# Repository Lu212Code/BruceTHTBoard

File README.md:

# BruceTHTBoard
Bruce PCB made for simple THT parts and Boards

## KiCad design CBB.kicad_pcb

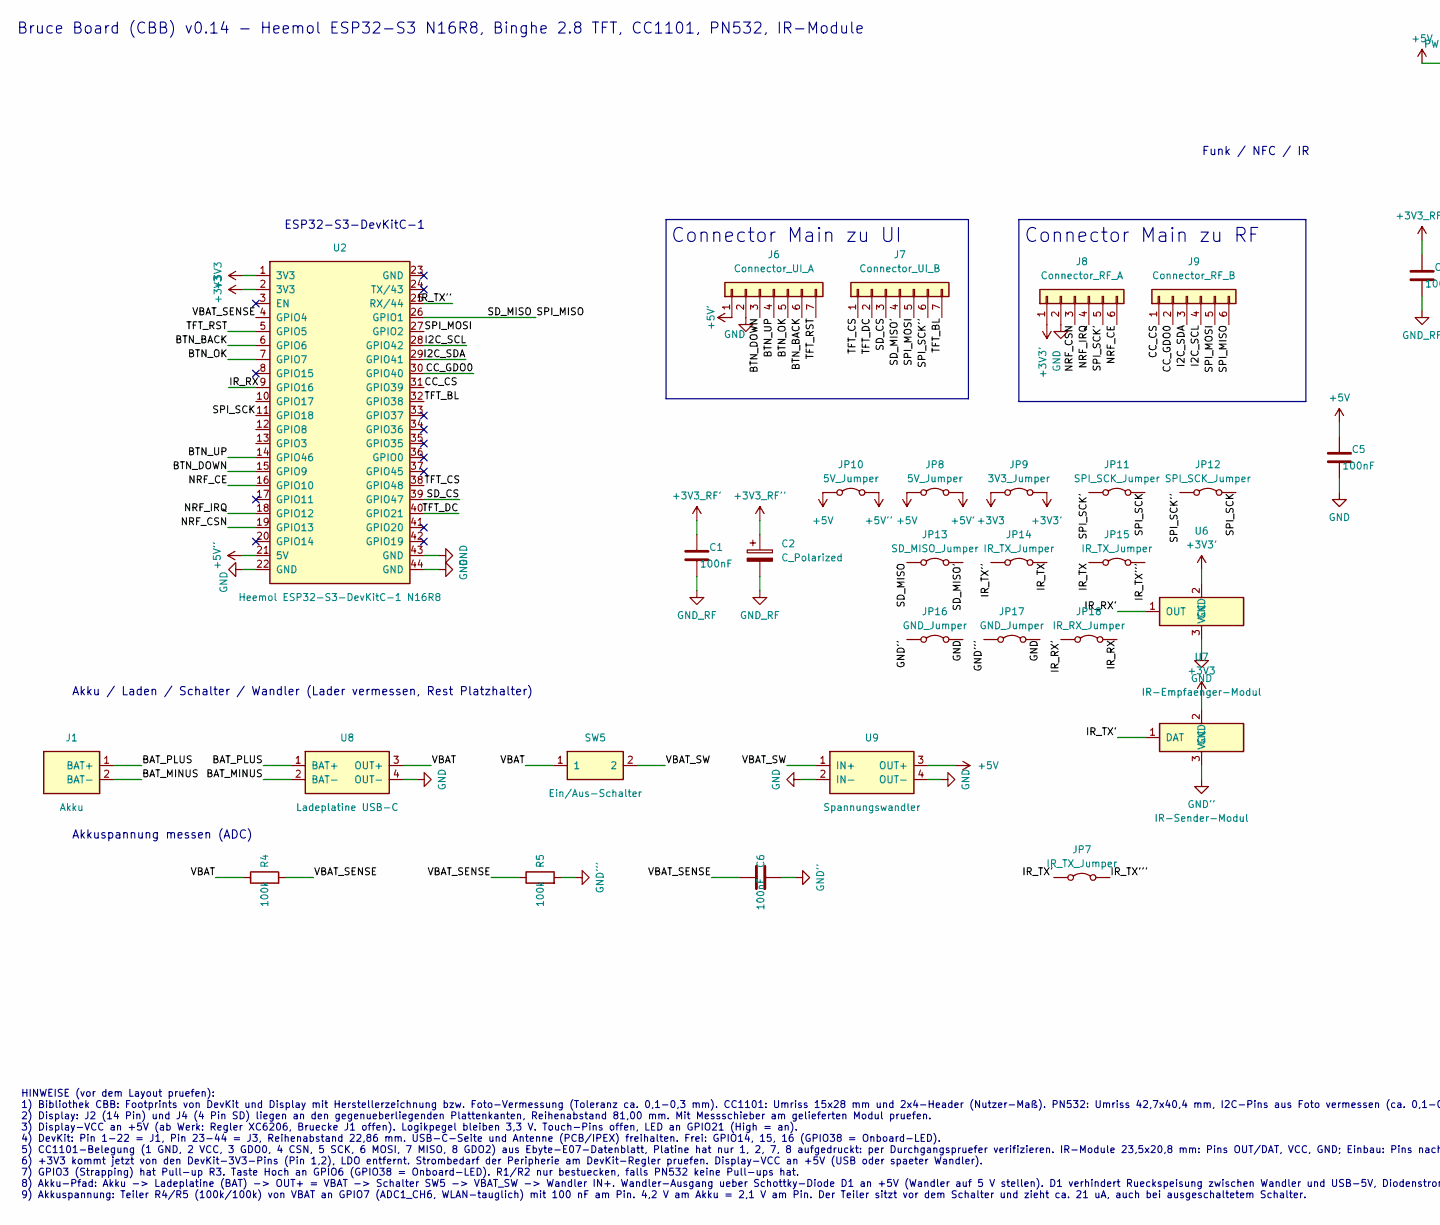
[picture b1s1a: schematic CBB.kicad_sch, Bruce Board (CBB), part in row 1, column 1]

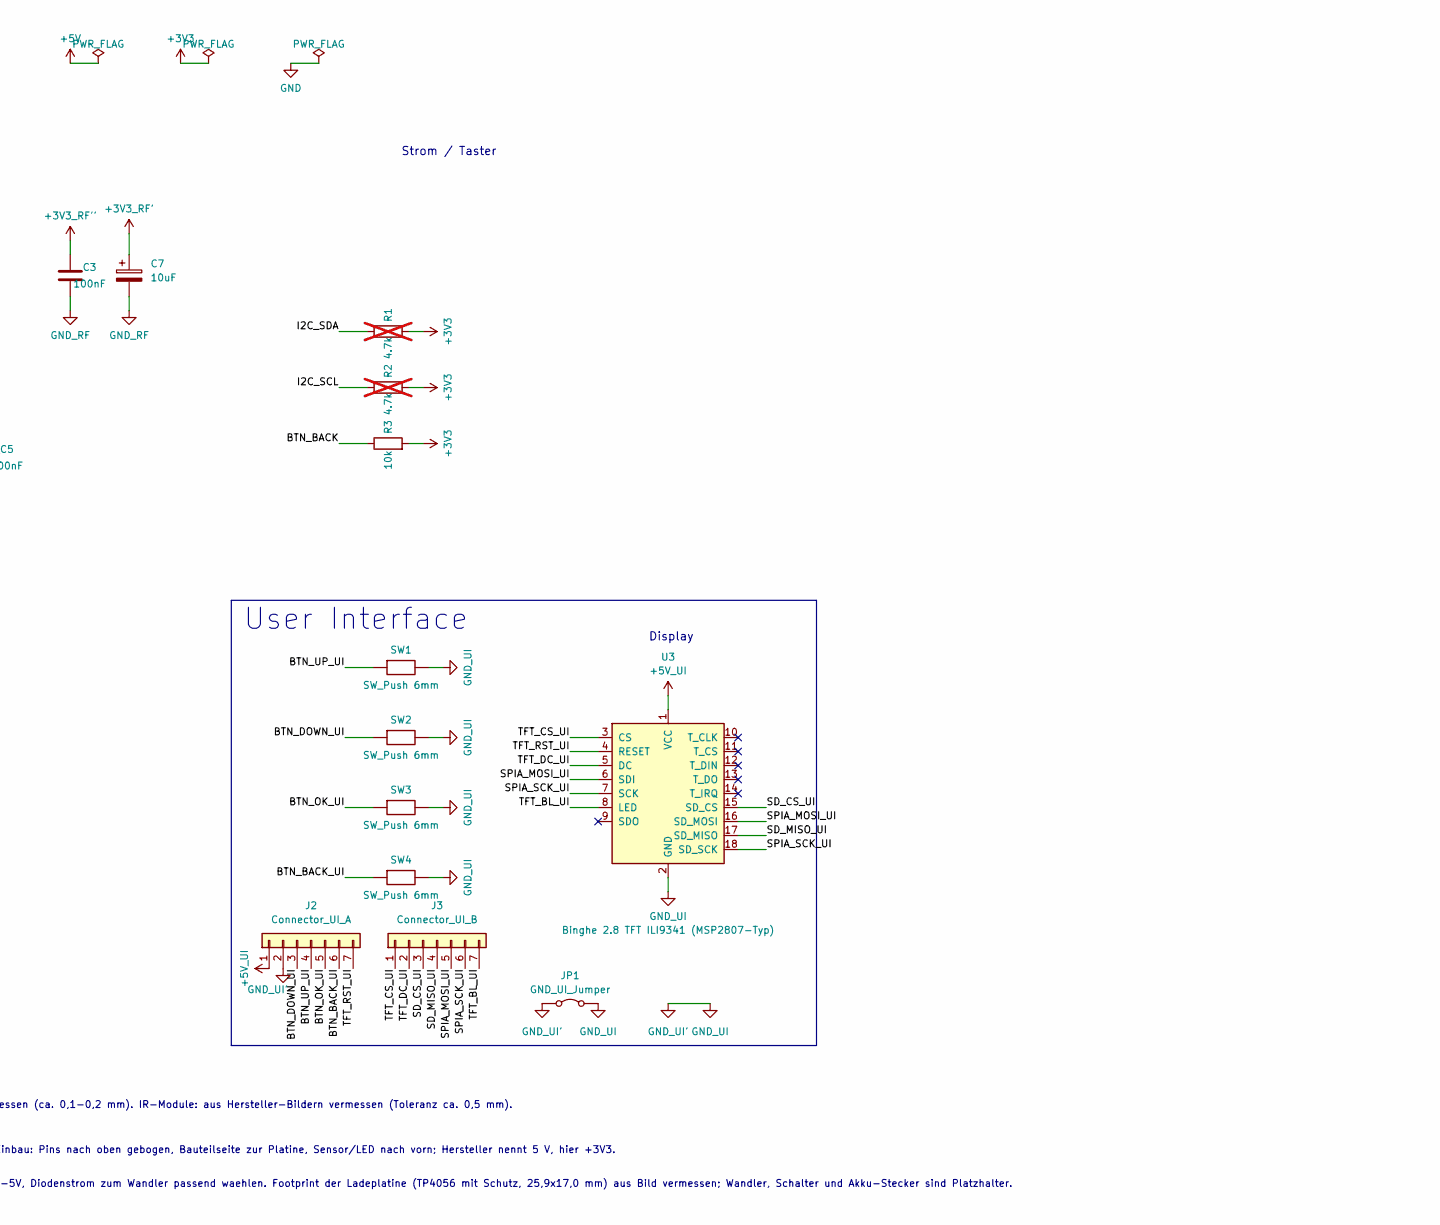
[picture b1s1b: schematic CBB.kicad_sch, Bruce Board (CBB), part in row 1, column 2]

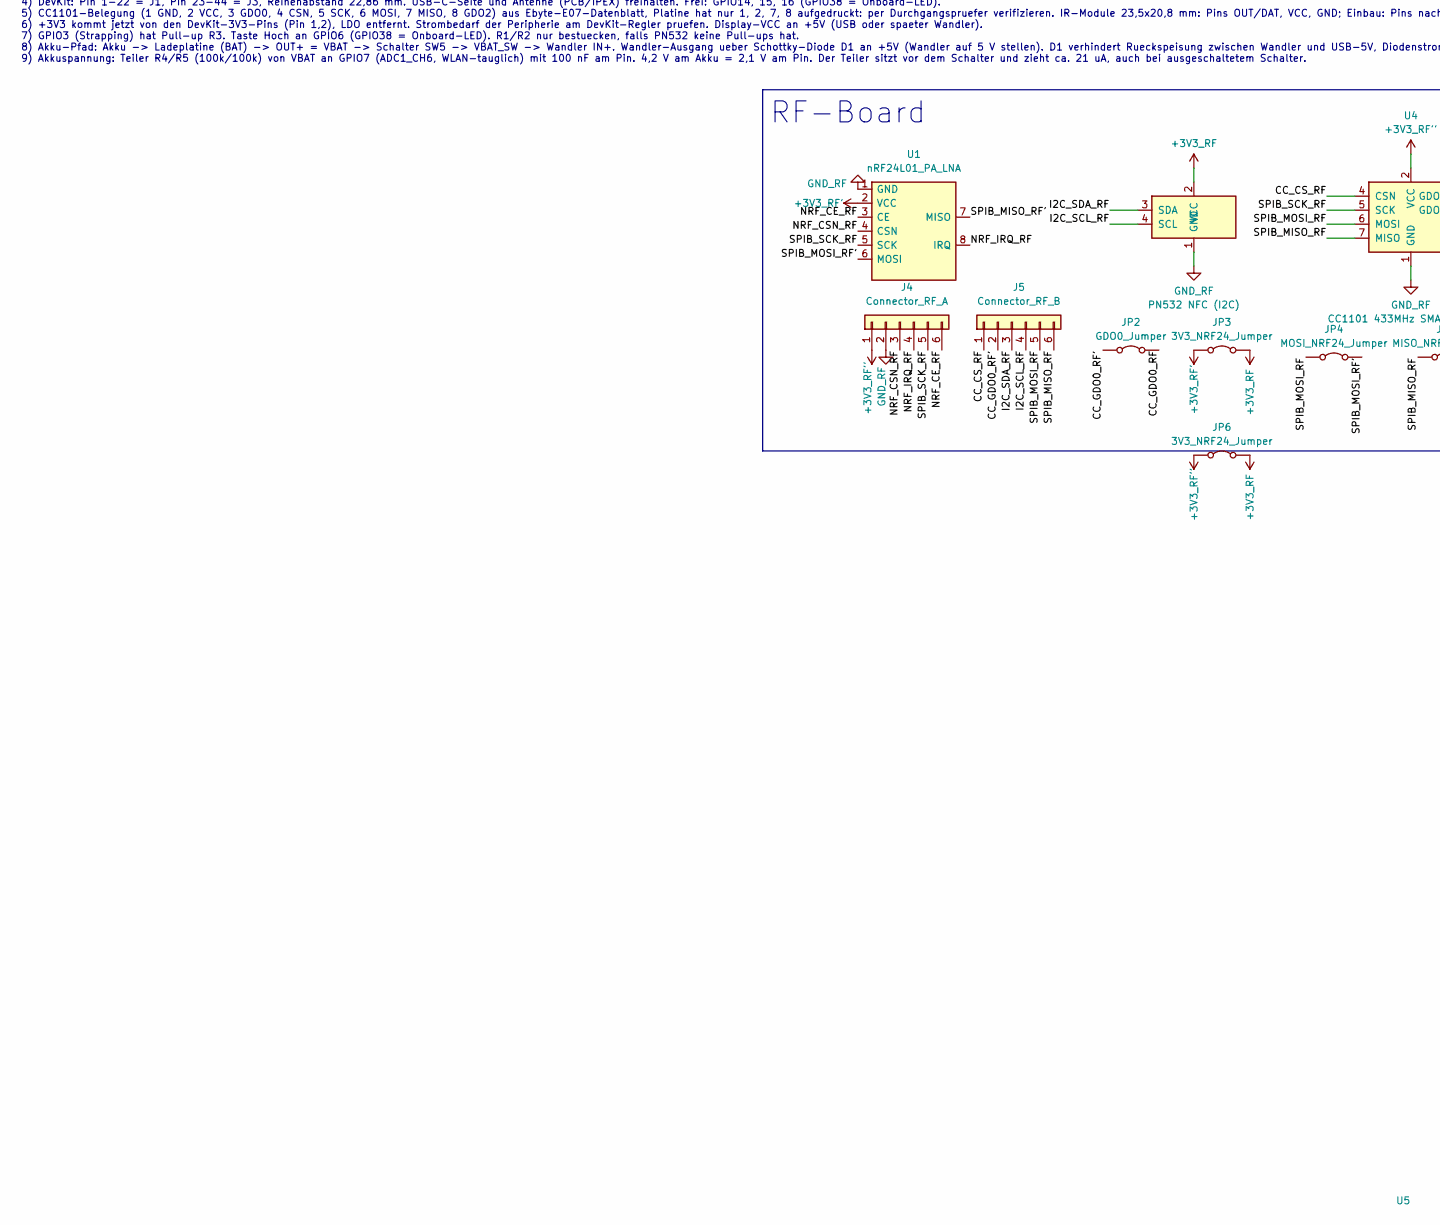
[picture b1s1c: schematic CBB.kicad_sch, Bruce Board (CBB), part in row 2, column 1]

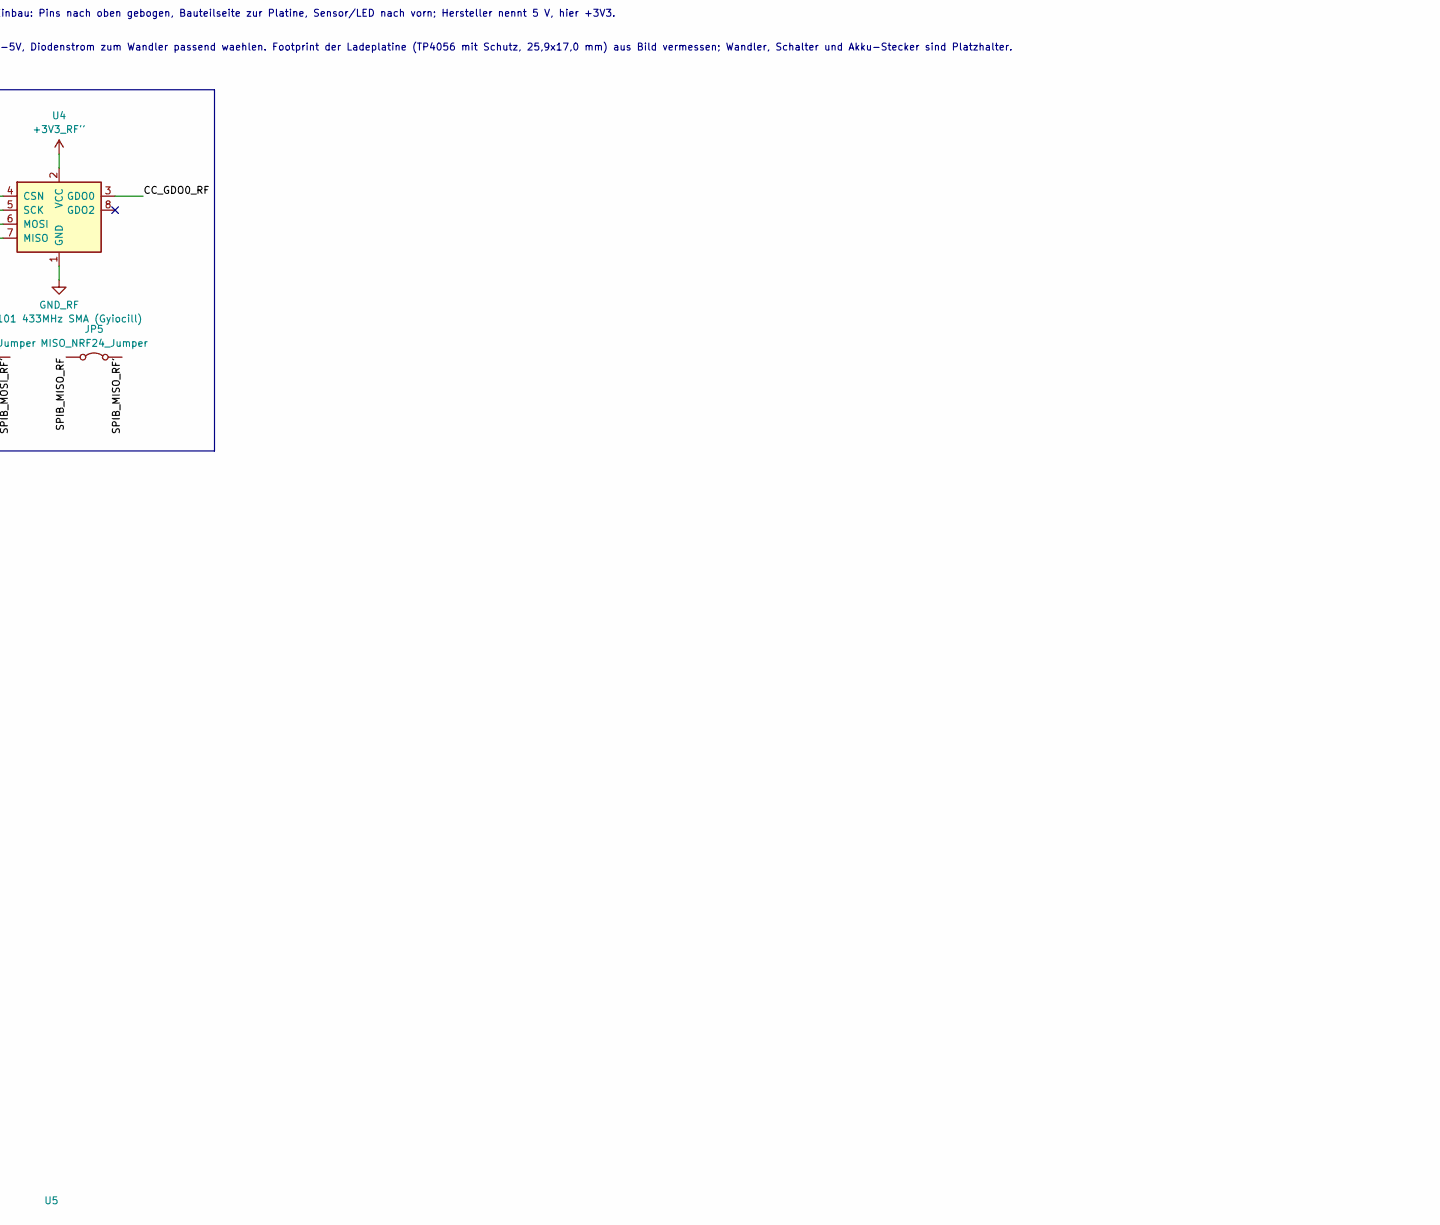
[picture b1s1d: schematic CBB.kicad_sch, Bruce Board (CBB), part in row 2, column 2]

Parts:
C1, C3, C5, C6: 100nF; C_Disc_D5.0mm_W2.5mm_P5.00mm
C2: C_Polarized; CP_Radial_D5.0mm_P2.00mm
C7: 10uF; CP_Radial_D5.0mm_P2.00mm
J1: Akku; PinHeader_1x02_P2.54mm_Vertical
J2, J6: Connector_UI_A; PinHeader_1x07_P2.54mm_Vertical
J3, J7: Connector_UI_B; PinHeader_1x07_P2.54mm_Vertical
J4, J8: Connector_RF_A; PinHeader_1x06_P2.54mm_Vertical
J5, J9: Connector_RF_B; PinHeader_1x06_P2.54mm_Vertical
JP1: GND_UI_Jumper; R_Axial_DIN0207_L6.3mm_D2.5mm_P10.16mm_Horizontal
JP2: GDO0_Jumper; R_Axial_DIN0207_L6.3mm_D2.5mm_P10.16mm_Horizontal
JP3, JP6: 3V3_NRF24_Jumper; R_Axial_DIN0207_L6.3mm_D2.5mm_P10.16mm_Horizontal
JP4: MOSI_NRF24_Jumper; R_Axial_DIN0207_L6.3mm_D2.5mm_P10.16mm_Horizontal
JP5: MISO_NRF24_Jumper; R_Axial_DIN0207_L6.3mm_D2.5mm_P10.16mm_Horizontal
JP7, JP14, JP15: IR_TX_Jumper; R_Axial_DIN0207_L6.3mm_D2.5mm_P10.16mm_Horizontal
JP8, JP10: 5V_Jumper; R_Axial_DIN0207_L6.3mm_D2.5mm_P10.16mm_Horizontal
JP9: 3V3_Jumper; R_Axial_DIN0207_L6.3mm_D2.5mm_P10.16mm_Horizontal
JP11, JP12: SPI_SCK_Jumper; R_Axial_DIN0207_L6.3mm_D2.5mm_P10.16mm_Horizontal
JP13: SD_MISO_Jumper; R_Axial_DIN0207_L6.3mm_D2.5mm_P10.16mm_Horizontal
JP16, JP17: GND_Jumper; R_Axial_DIN0207_L6.3mm_D2.5mm_P10.16mm_Horizontal
JP18: IR_RX_Jumper; R_Axial_DIN0207_L6.3mm_D2.5mm_P10.16mm_Horizontal
R1, R2: 4.7k; R_Axial_DIN0207_L6.3mm_D2.5mm_P10.16mm_Horizontal; not fitted
R3: 10k; R_Axial_DIN0207_L6.3mm_D2.5mm_P10.16mm_Horizontal
R4, R5: 100k; R_Axial_DIN0207_L6.3mm_D2.5mm_P10.16mm_Horizontal
SW1, SW2, SW3, SW4: SW_Push 6mm; SW_PUSH_6mm
SW5: Ein/Aus-Schalter; Switch-Placeholder_1x02
U1: nRF24L01_PA_LNA; nRF24L01_PA_LNA_41x15.5mm_2x4_P2.54mm
U2: Heemol ESP32-S3-DevKitC-1 N16R8; ESP32-S3-DevKitC-1_62.74x25.4mm
U3: Binghe 2.8 TFT ILI9341 (MSP2807-Typ); TFT-2.8in-ILI9341-MSP2807_50x86mm_14p+4p
U4: CC1101 433MHz SMA (Gyiocill); CC1101-Module_15x28mm_2x04
U5: PN532 NFC (I2C); PN532-NFC-Module_42.7x40.4mm_1x04
U6: IR-Empfaenger-Modul; IR-Receiver-Module_23.5x20.8mm_1x03
U7: IR-Sender-Modul; IR-Transmitter-Module_23.5x20.8mm_1x03
U8: Ladeplatine USB-C; Charger-Module_TP4056_25.9x17.0mm_1x04
U9: Spannungswandler; Converter-Module_Placeholder_1x04

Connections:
+3V3: JP9.1 (A), R1.2, R2.2, R3.2, U2.1 (3V3), U2.2 (3V3), U7.2 (VCC)
+3V3': J8.1, JP9.2 (B), U6.2 (VCC)
+3V3_RF: JP3.2 (B), JP6.2 (B), U5.2 (VCC)
+3V3_RF': C1.1, C7.1, JP3.1 (A), U1.2 (VCC)
+3V3_RF'': C2.1, C3.1, J4.1, JP6.1 (A), U4.2 (VCC)
+5V: C5.1, JP8.1 (A), JP10.1 (A), U9.3 (OUT+)
+5V': J6.1, JP8.2 (B)
+5V'': JP10.2 (B), U2.21 (5V)
+5V_UI: J2.1, U3.1 (VCC)
/BAT_MINUS: J1.2 (BAT-), U8.2 (BAT-)
/BAT_PLUS: J1.1 (BAT+), U8.1 (BAT+)
/BTN_BACK: J6.6, R3.1, U2.6 (GPIO6)
/BTN_BACK_UI: J2.6, SW4.1
/BTN_DOWN: J6.3, U2.15 (GPIO9)
/BTN_DOWN_UI: J2.3, SW2.1
/BTN_OK: J6.5, U2.7 (GPIO7)
/BTN_OK_UI: J2.5, SW3.1
/BTN_UP: J6.4, U2.14 (GPIO46)
/BTN_UP_UI: J2.4, SW1.1
/CC_CS: J9.1, U2.31 (GPIO39)
/CC_CS_RF: J5.1, U4.4 (CSN)
/CC_GDO0: J9.2, U2.30 (GPIO40)
/CC_GDO0_RF: JP2.2 (B), U4.3 (GDO0)
/CC_GDO0_RF': J5.2, JP2.1 (A)
/I2C_SCL: J9.4, R2.1, U2.28 (GPIO42)
/I2C_SCL_RF: J5.4, U5.4 (SCL)
/I2C_SDA: J9.3, R1.1, U2.29 (GPIO41)
/I2C_SDA_RF: J5.3, U5.3 (SDA)
/IR_RX: JP18.2 (B), U2.9 (GPIO16)
/IR_RX': JP18.1 (A), U6.1 (OUT)
/IR_TX: JP14.2 (B), JP15.1 (A)
/IR_TX': JP7.1 (A), U7.1 (DAT)
/IR_TX'': JP14.1 (A), U2.25 (RX/44)
/IR_TX''': JP7.2 (B), JP15.2 (B)
/NRF_CE: J8.6, U2.16 (GPIO10)
/NRF_CE_RF: J4.6, U1.3 (CE)
/NRF_CSN: J8.3, U2.19 (GPIO13)
/NRF_CSN_RF: J4.3, U1.4 (CSN)
/NRF_IRQ: J8.4, U2.18 (GPIO12)
/NRF_IRQ_RF: J4.4, U1.8 (IRQ)
/SD_CS: J7.3, U2.39 (GPIO47)
/SD_CS_UI: J3.3, U3.15 (SD_CS)
/SD_MISO: J9.6, JP13.1 (A), U2.26 (GPIO1)
/SD_MISO': J7.4, JP13.2 (B)
/SD_MISO_UI: J3.4, U3.17 (SD_MISO)
/SPIA_MOSI_UI: J3.5, U3.6 (SDI), U3.16 (SD_MOSI)
/SPIA_SCK_UI: J3.6, U3.7 (SCK), U3.18 (SD_SCK)
/SPIB_MISO_RF: J5.6, JP5.1 (A), U4.7 (MISO)
/SPIB_MISO_RF': JP5.2 (B), U1.7 (MISO)
/SPIB_MOSI_RF: J5.5, JP4.1 (A), U4.6 (MOSI)
/SPIB_MOSI_RF': JP4.2 (B), U1.6 (MOSI)
/SPIB_SCK_RF: J4.5, U1.5 (SCK), U4.5 (SCK)
/SPI_MOSI: J7.5, J9.5, U2.27 (GPIO2)
/SPI_SCK: JP11.2 (B), JP12.2 (B), U2.11 (GPIO18)
/SPI_SCK': J8.5, JP11.1 (A)
/SPI_SCK'': J7.6, JP12.1 (A)
/TFT_BL: J7.7, U2.32 (GPIO38)
/TFT_BL_UI: J3.7, U3.8 (LED)
/TFT_CS: J7.1, U2.38 (GPIO48)
/TFT_CS_UI: J3.1, U3.3 (CS)
/TFT_DC: J7.2, U2.40 (GPIO21)
/TFT_DC_UI: J3.2, U3.5 (DC)
/TFT_RST: J6.7, U2.5 (GPIO5)
/TFT_RST_UI: J2.7, U3.4 (RESET)
/VBAT: R4.1, SW5.1, U8.3 (OUT+)
/VBAT_SENSE: C6.1, R4.2, R5.1, U2.4 (GPIO4)
/VBAT_SW: SW5.2, U9.1 (IN+)
GND: C5.2, J6.2, J8.2, JP16.2 (B), JP17.2 (B), U2.22 (GND), U2.43 (GND), U2.44 (GND), U6.3 (GND), U8.4 (OUT-), U9.2 (IN-), U9.4 (OUT-)
GND'': C6.2, JP16.1 (A), U7.3 (GND)
GND''': JP17.1 (A), R5.2
GND_RF: C1.2, C2.2, C3.2, C7.2, J4.2, U1.1 (GND), U4.1 (GND), U5.1 (GND)
GND_UI: J2.2, JP1.1 (A), JP1.2 (B), SW1.2, SW2.2, SW3.2, SW4.2, U3.2 (GND)

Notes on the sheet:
Display
Strom / Taster
Akkuspannung messen (ADC)
Bruce Board (CBB) v0.14 - Heemol ESP32-S3 N16R8, Binghe 2.8 TFT, CC1101, PN532, IR-Module
ESP32-S3-DevKitC-1
Connector Main zu RF
HINWEISE (vor dem Layout pruefen): 1) Bibliothek CBB: Footprints von DevKit und Display mit Herstellerzeichnung bzw. Foto-Vermessung (Toleranz ca. 0,1-0,3 mm). CC1101: Umriss 15x28 mm und 2x4-Header (Nutzer-Maß). PN532: Umriss 42,7x40,4 mm, I2C-Pins aus Foto vermessen (ca. 0,1-0,2 mm). IR-Module: a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
RF-Board
Connector Main zu UI
Funk / NFC / IR
Akku / Laden / Schalter / Wandler (Lader vermessen, Rest Platzhalter)
User Interface

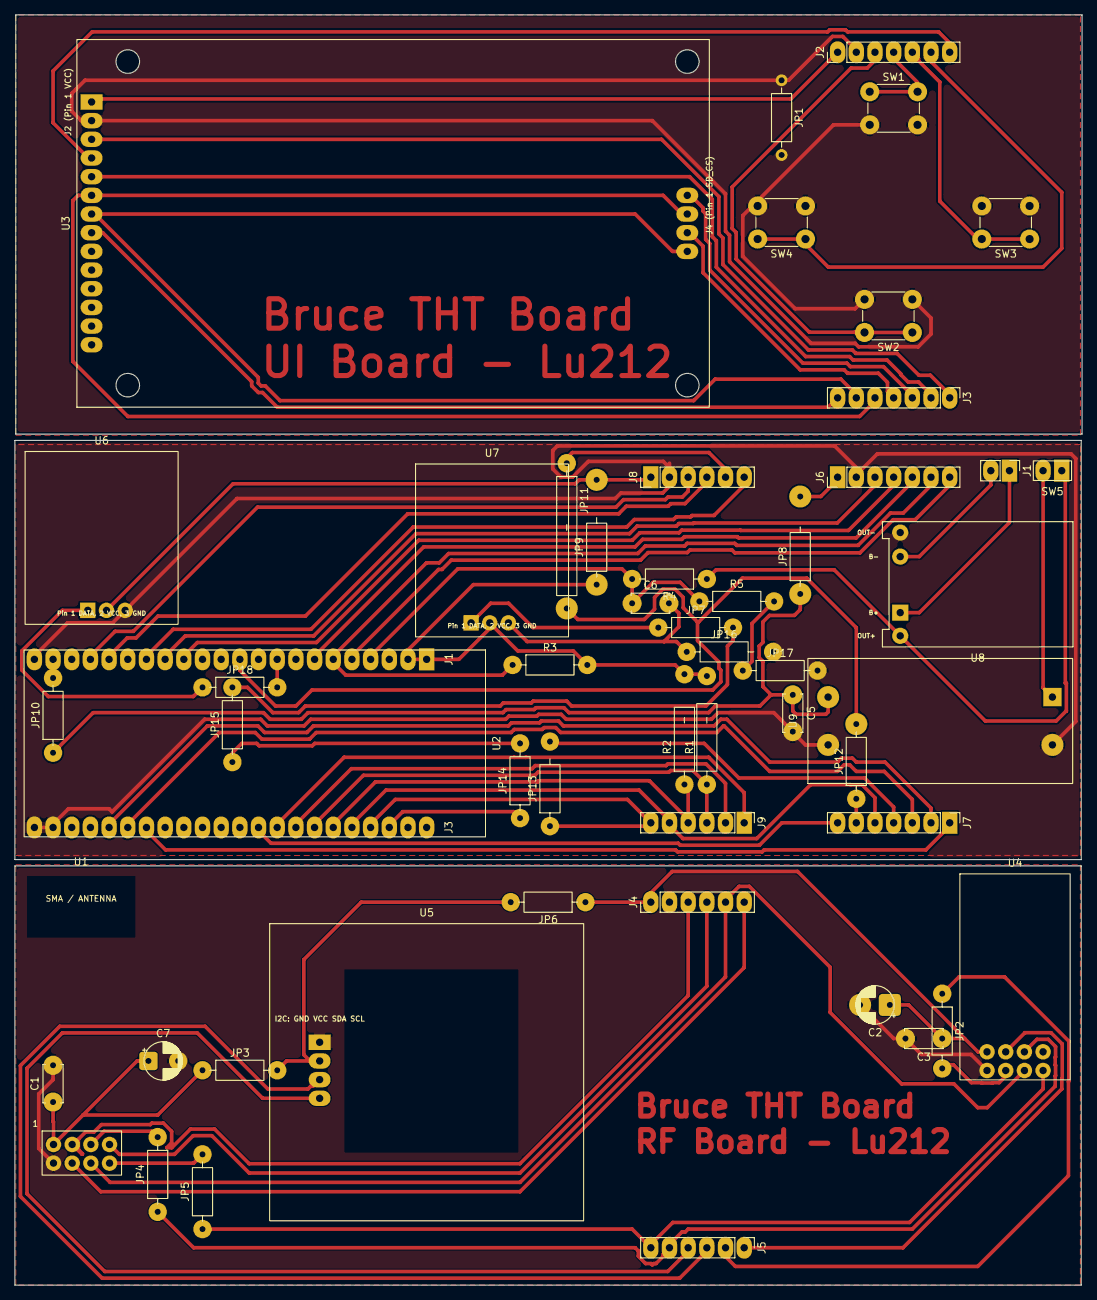
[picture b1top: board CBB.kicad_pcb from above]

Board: 2 copper layers, 145.1 x 172.7 mm, 52 parts (0 on the bottom side), 72 nets.
